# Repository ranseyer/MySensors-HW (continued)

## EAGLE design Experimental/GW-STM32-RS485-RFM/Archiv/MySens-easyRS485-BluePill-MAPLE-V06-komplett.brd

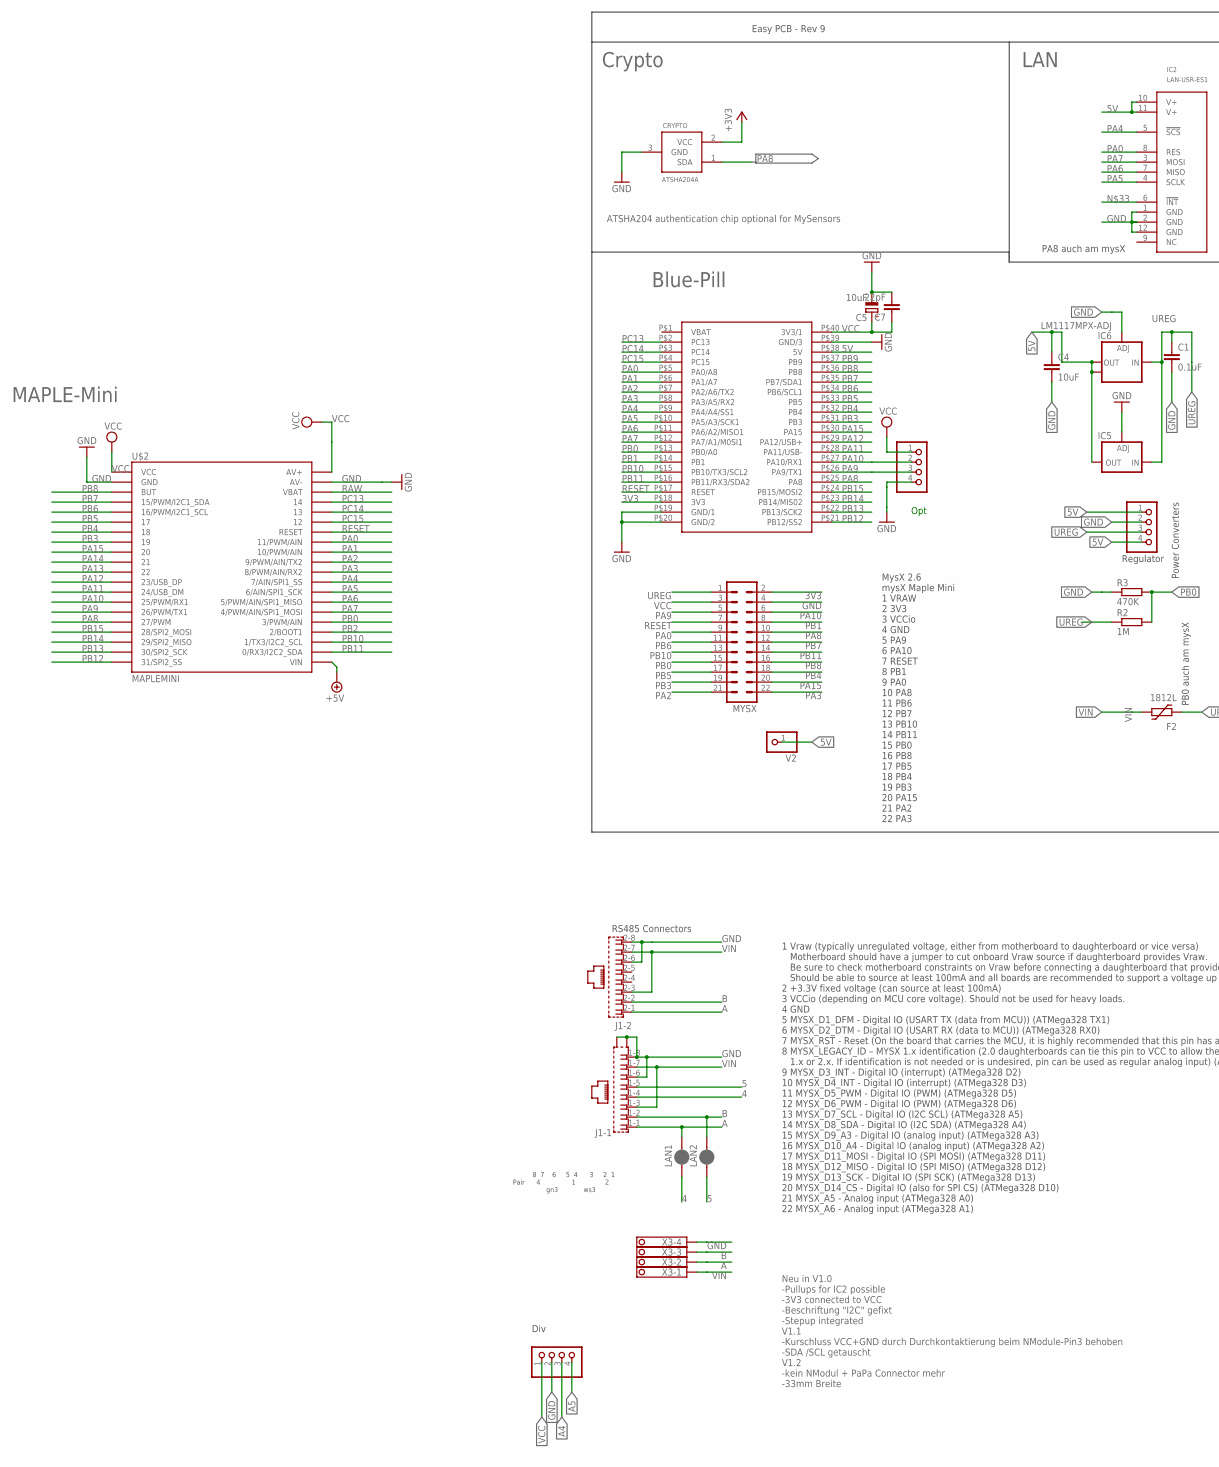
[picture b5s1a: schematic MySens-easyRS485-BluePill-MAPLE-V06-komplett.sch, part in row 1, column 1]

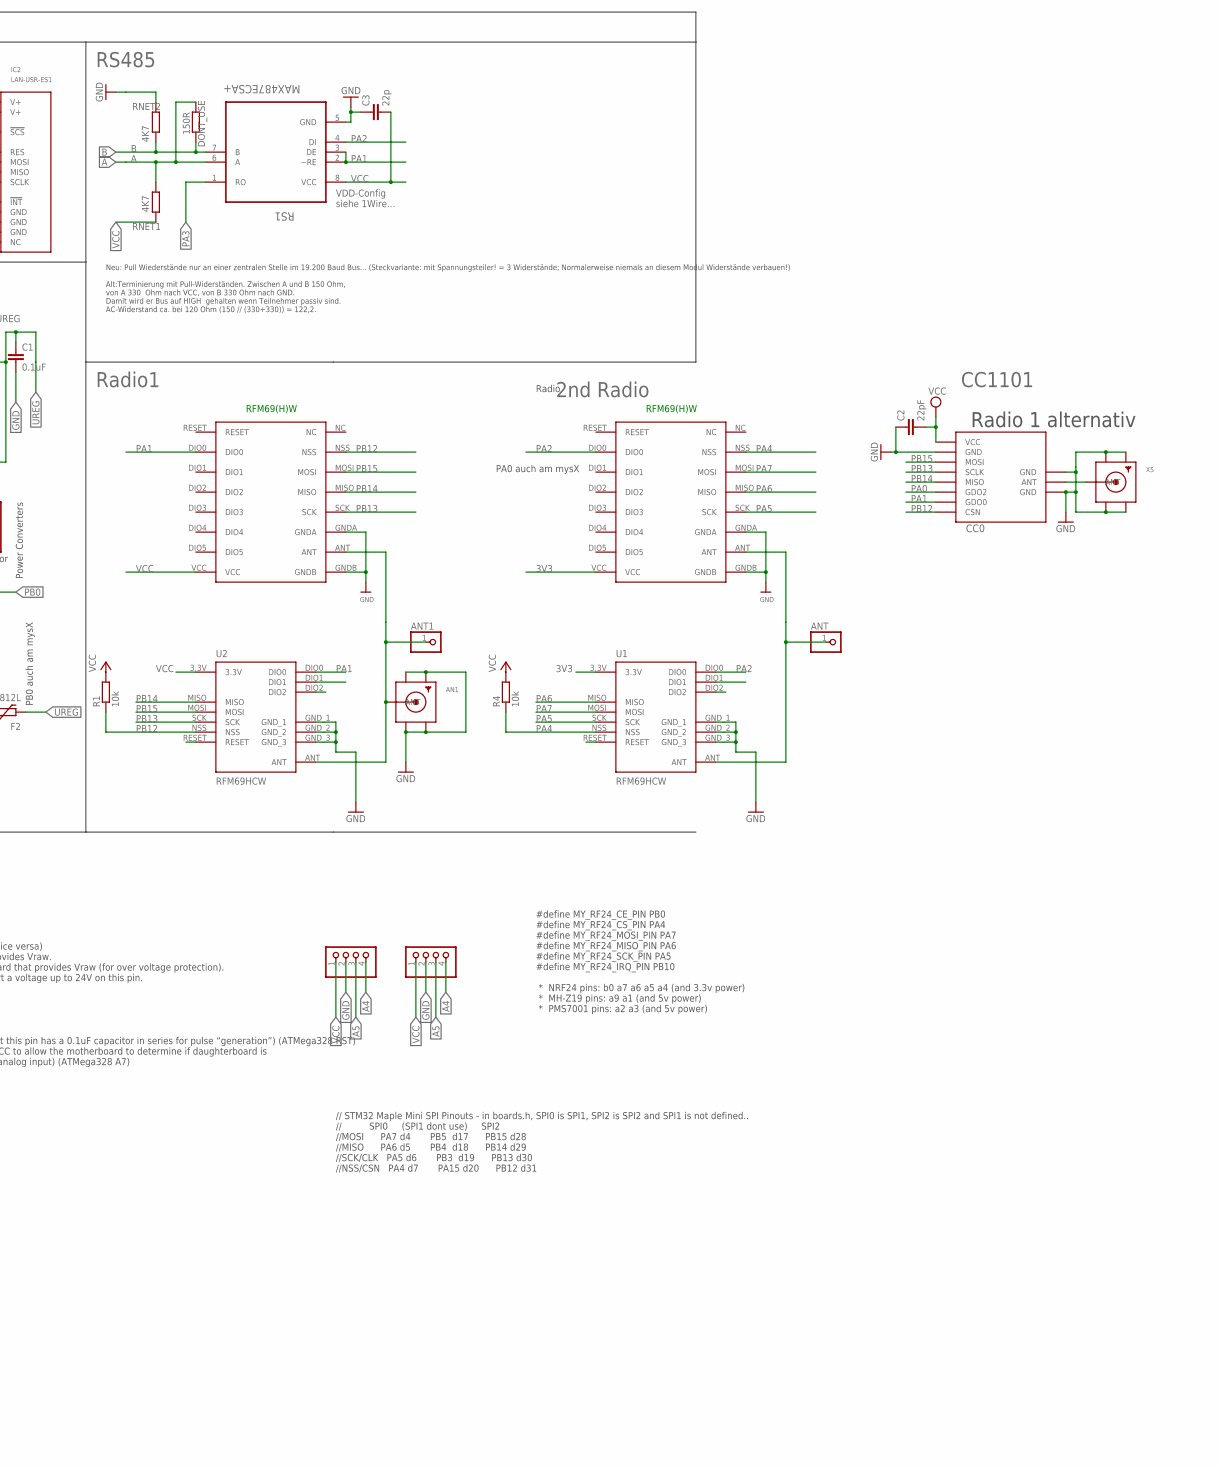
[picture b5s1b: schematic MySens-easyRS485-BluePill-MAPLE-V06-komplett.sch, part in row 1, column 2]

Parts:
AN1: SMACONNECTOR_EDGE; SMA_EDGELAUNCH
ANT, ANT1: PINHD-1X1; 1X01
BH1750: PINHD-1X04_2.54-S; 1X04-S
C1: 0.1uF; C1206
C2, C7: 22pF; C0805
C3: 22p; C0805
C4: 10uF; C1210
C5: 10uF; R/2012-12W
CC0: CC1101; CC1101_MODULE1_SMD
CRYPTO: ATSHA204A; SOT23
DBG: PINHD-1X04_2.54-S; 1X04-S
DONT_USE: 150R; R0805
F2: 1812L
I2C-1, I2C-2: PINHD-1X04_2.54-S; 1X04-S
IC2: LAN-USR-ES1; USR-ES1
IC5: LD117ADT50TR; DPACK
IC6: LM1117MPX-ADJ; SOT223
J1: RJ45_2X_NARROW_SHILDPINS_NOCASE
LAN1, LAN2: JUMPER-SMT_2_NC_PASTE_SILK; SMT-JUMPER_2_NC_PASTE_SILK
MYSX: MA11-2
R1, R4: 10k; M0805
R2: 1M; R0805
R3: 470K; R0805
RFM69W, RFM69W1: RFM69HW; RFM
RNET1, RNET2: 4K7; R0805
RS1: MAX487ECSA+; SOIC127P600X175-8N
STEPDWN: PINHD-1X04_2.54-S; 1X04-S
U1, U2: RFM69HCW; RFM69HCW-XXXS2
U$2: MAPLEMINI; 20-DIP
U$4: BLUEPILL
V2: PINHD-1X1; 1X01
X3: 1751264
X5: SMACONNECTOR_EDGE; SMA_EDGELAUNCH

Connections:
3V3: CRYPTO.2 (VCC), MYSX.2, RFM69W.VCC, U1.3.3V, U$4.P$18 (3V3)
4: J1.1-4 (4), LAN1.1
5: J1.1-5 (5), LAN2.1
5V: C4.1, IC2.10 (V+), IC2.11 (V+), IC5.4 (OUT), IC6.2 (OUT), IC6.TAB (OUT1), STEPDWN.1, STEPDWN.4, U$4.P$38 (5V), V2.1
+5V: U$2.21 (VIN)
A: DONT_USE.1, J1.1-1 (1), J1.2-1 (1), LAN1.2, RNET1.2, RS1.6 (A), X3.2
A4: BH1750.4, I2C-1.4, I2C-2.3
A5: BH1750.3, I2C-1.3, I2C-2.4
ANT0: CC0.ANT, X5.P (ANT)
ANT1: AN1.P (ANT), ANT1.1, RFM69W1.ANT, U2.ANT
ANT2: ANT.1, RFM69W.ANT, U1.ANT
B: DONT_USE.2, J1.1-2 (2), J1.2-2 (2), LAN2.2, RNET2.1, RS1.7 (B), X3.3
GND: AN1.GND@1 (GND4), AN1.GND@2 (GND3), AN1.GND@3 (GND2), AN1.GND@4 (GND1), BH1750.2, C1.2, C2.1, C3.1, C4.2, C5.-, C7.2, CC0.GND@0 (GND), CC0.GND@1 (GND), CC0.GND@2 (GND), CRYPTO.3 (GND), DBG.4, I2C-1.2, I2C-2.2, IC2.1 (GND), IC2.2 (GND), IC2.12 (GND), IC5.1 (ADJ), IC6.1 (ADJ), J1.1-6 (6), J1.1-8 (8), J1.2-6 (6), J1.2-8 (8), J1.G1 (S1), J1.G3 (S2), MYSX.4, R3.1, RFM69W.GNDA, RFM69W.GNDB, RFM69W1.GNDA, RFM69W1.GNDB, RNET2.2, RS1.5 (GND), STEPDWN.2, U1.GND_1, U1.GND_2, U1.GND_3, U2.GND_1, U2.GND_2, U2.GND_3, U$2.2 (GND), U$2.39 (AV-), U$4.P$19 (GND/1), U$4.P$20 (GND/2), U$4.P$39 (GND/3), X3.4, X5.GND@1 (GND4), X5.GND@2 (GND3), X5.GND@3 (GND2), X5.GND@4 (GND1)
PA0: CC0.GDO2, IC2.8 (RES), MYSX.9, U$2.33 (11/PWM/AIN), U$4.P$5 (PA0/A8)
PA1: CC0.GDO0, RFM69W1.DIO0, RS1.2 (~RE), RS1.3 (DE), U2.DIO0, U$2.32 (10/PWM/AIN), U$4.P$6 (PA1/A7)
PA2: MYSX.21, RFM69W.DIO0, RS1.4 (DI), U1.DIO0, U$2.31 (9/PWM/AIN/TX2), U$4.P$7 (PA2/A6/TX2)
PA3: MYSX.22, RS1.1 (RO), U$2.30 (8/PWM/AIN/RX2), U$4.P$8 (PA3/A5/RX2)
PA4: IC2.5 (!SCS!), R4.1, RFM69W.NSS, U1.NSS, U$2.29 (7/AIN/SPI1_SS), U$4.P$9 (PA4/A4/SS1)
PA5: IC2.4 (SCLK), RFM69W.SCK, U1.SCK, U$2.28 (6/AIN/SPI1_SCK), U$4.P$10 (PA5/A3/SCK1)
PA6: IC2.7 (MISO), RFM69W.MISO, U1.MISO, U$2.27 (5/PWM/AIN/SPI1_MISO), U$4.P$11 (PA6/A2/MISO1)
PA7: IC2.3 (MOSI), RFM69W.MOSI, U1.MOSI, U$2.26 (4/PWM/AIN/SPI1_MOSI), U$4.P$12 (PA7/A1/M0SI1)
PA8: CRYPTO.1 (SDA), MYSX.10, U$2.16 (27/PWM), U$4.P$25 (PA8)
PA9: DBG.3, MYSX.5, U$2.15 (26/PWM/TX1), U$4.P$26 (PA9/TX1)
PA10: DBG.2, MYSX.6, U$2.14 (25/PWM/RX1), U$4.P$27 (PA10/RX1)
PA11: U$2.13 (24/USB_DM), U$4.P$28 (PA11/USB-)
PA12: U$2.12 (23/USB_DP), U$4.P$29 (PA12/USB+)
PA13: U$2.11 (22)
PA14: U$2.10 (21)
PA15: MYSX.20, U$2.9 (20), U$4.P$30 (PA15)
PB0: MYSX.15, R2.2, R3.2, U$2.25 (3/PWM/AIN), U$4.P$13 (PB0/A0)
PB1: MYSX.8, U$4.P$14 (PB1)
PB2: U$2.24 (2/BOOT1)
PB3: MYSX.19, U$2.8 (19), U$4.P$31 (PB3)
PB4: MYSX.18, U$2.7 (18), U$4.P$32 (PB4)
PB5: MYSX.17, U$2.6 (17), U$4.P$33 (PB5)
PB6: MYSX.11, U$2.5 (16/PWM/I2C1_SCL), U$4.P$34 (PB6/SCL1)
PB7: MYSX.12, U$2.4 (15/PWM/I2C1_SDA), U$4.P$35 (PB7/SDA1)
PB8: MYSX.16, U$2.3 (BUT), U$4.P$36 (PB8)
PB9: U$4.P$37 (PB9)
PB10: MYSX.13, U$2.23 (1/TX3/I2C2_SCL), U$4.P$15 (PB10/TX3/SCL2)
PB11: MYSX.14, U$2.22 (0/RX3/I2C2_SDA), U$4.P$16 (PB11/RX3/SDA2)
PB12: CC0.CSN, R1.1, RFM69W1.NSS, U2.NSS, U$2.20 (31/SPI2_SS), U$4.P$21 (PB12/SS2)
PB13: CC0.SCLK, RFM69W1.SCK, U2.SCK, U$2.19 (30/SPI2_SCK), U$4.P$22 (PB13/SCK2)
PB14: CC0.MISO, RFM69W1.MISO, U2.MISO, U$2.18 (29/SPI2_MISO), U$4.P$23 (PB14/MIS02)
PB15: CC0.MOSI, RFM69W1.MOSI, U2.MOSI, U$2.17 (28/SPI2_MOSI), U$4.P$24 (PB15/MOSI2)
PC13: U$2.37 (14), U$4.P$2 (PC13)
PC14: U$2.36 (13), U$4.P$3 (PC14)
PC15: U$2.35 (12), U$4.P$4 (PC15)
RAW: U$2.38 (VBAT)
RESET: MYSX.7, U$2.34 (RESET), U$4.P$17 (RESET)
UREG: C1.1, F2.P$1 (1), IC5.3 (IN), IC6.3 (IN), MYSX.1, R2.1, STEPDWN.3
VCC: BH1750.1, C2.2, C3.2, C5.+, C7.1, CC0.VCC, DBG.1, I2C-1.1, I2C-2.1, MYSX.3, R1.2, R4.2, RFM69W1.VCC, RNET1.1, RS1.8 (VCC), U2.3.3V, U$2.1 (VCC), U$2.40 (AV+), U$4.P$40 (3V3/1)
VIN: F2.P$2 (2), J1.1-3 (3), J1.1-7 (7), J1.2-3 (3), J1.2-7 (7), X3.1

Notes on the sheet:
Easy PCB - Rev 9
ATSHA204 authentication chip optional for MySensors
RFM69(H)W
Radio
VDD-Config siehe 1Wire...
Neu: Pull Wiederstände nur an einer zentralen Stelle im 19.200 Baud Bus... (Steckvariante: mit Spannungsteiler! = 3 Widerstände; Normalerweise niemals an diesem Modul Widerstände verbauen!) Alt:Terminierung mit Pull-Widerständen. Zwischen A und B 150 Ohm, von A 330 Ohm nach VCC, von B 330 Ohm nach 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
Opt
Blue-Pill
// STM32 Maple Mini SPI Pinouts - in boards.h, SPI0 is SPI1, SPI2 is SPI2 and SPI1 is not defined.. // SPI0 (SPI1 dont use) SPI2 //MOSI PA7 d4 PB5 d17 PB15 d28 //MISO PA6 d5 PB4 d18 PB14 d29 //SCK/CLK PA5 d6 PB3 d19 PB13 d30 //NSS/CSN PA4 d7 PA15 d20 PB12 d31
#define MY_RF24_CE_PIN PB0 #define MY_RF24_CS_PIN PA4 #define MY_RF24_MOSI_PIN PA7 #define MY_RF24_MISO_PIN PA6 #define MY_RF24_SCK_PIN PA5 #define MY_RF24_IRQ_PIN PB10 * NRF24 pins: b0 a7 a6 a5 a4 (and 3.3v power) * MH-Z19 pins: a9 a1 (and 5v power) * PMS7001 pins: a2 a3 (and 5v power)
Power Converters
Regulator
Div
Neu in V1.0 -Pullups for IC2 possible -3V3 connected to VCC -Beschriftung "I2C" gefixt -Stepup integrated V1.1 -Kurschluss VCC+GND durch Durchkontaktierung beim NModule-Pin3 behoben -SDA /SCL getauscht V1.2 -kein NModul + PaPa Connector mehr -33mm Breite
8 7 6 5 4 3 2 1 Pair 4 1 2 gn3 ws3
RS485 Connectors
1 Vraw (typically unregulated voltage, either from motherboard to daughterboard or vice versa) Motherboard should have a jumper to cut onboard Vraw source if daughterboard provides Vraw. Be sure to check motherboard constraints on Vraw before connecting a daughterboard that provides Vraw (for over 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
MysX 2.6 mysX Maple Mini 1 VRAW 2 3V3 3 VCCio 4 GND 5 PA9 6 PA10 7 RESET 8 PB1 9 PA0 10 PA8 11 PB6 12 PB7 13 PB10 14 PB11 15 PB0 16 PB8 17 PB5 18 PB4 19 PB3 20 PA15 21 PA2 22 PA3
PA0 auch am mysX
PB0 auch am mysX
PA8 auch am mysX
Radio1
2nd Radio
LAN
RS485
Crypto
Radio 1 alternativ
CC1101
MAPLE-Mini

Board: 2 copper layers, 41 parts (18 on the bottom side), 47 nets, no tracks yet.
